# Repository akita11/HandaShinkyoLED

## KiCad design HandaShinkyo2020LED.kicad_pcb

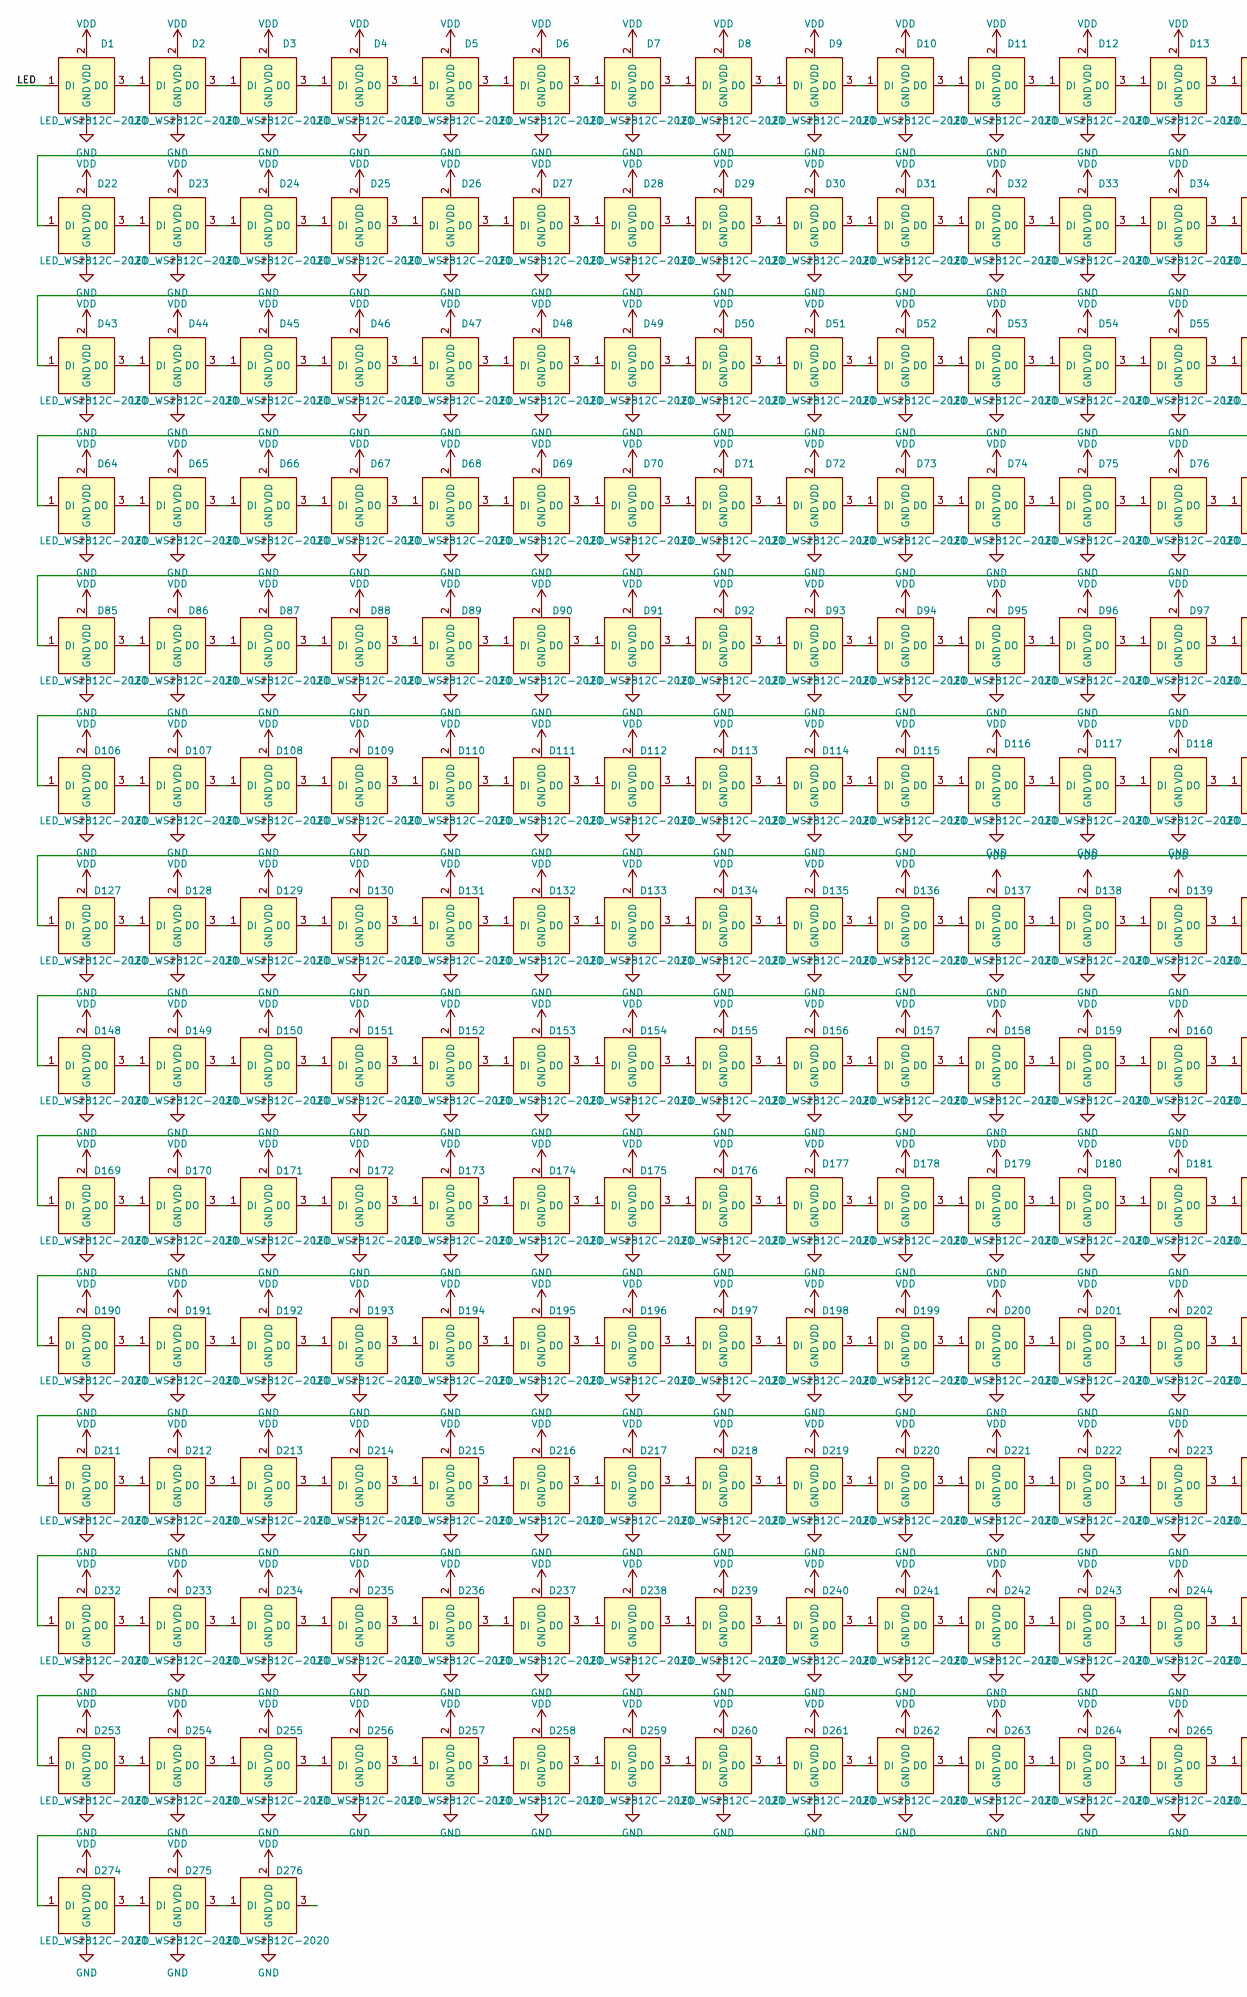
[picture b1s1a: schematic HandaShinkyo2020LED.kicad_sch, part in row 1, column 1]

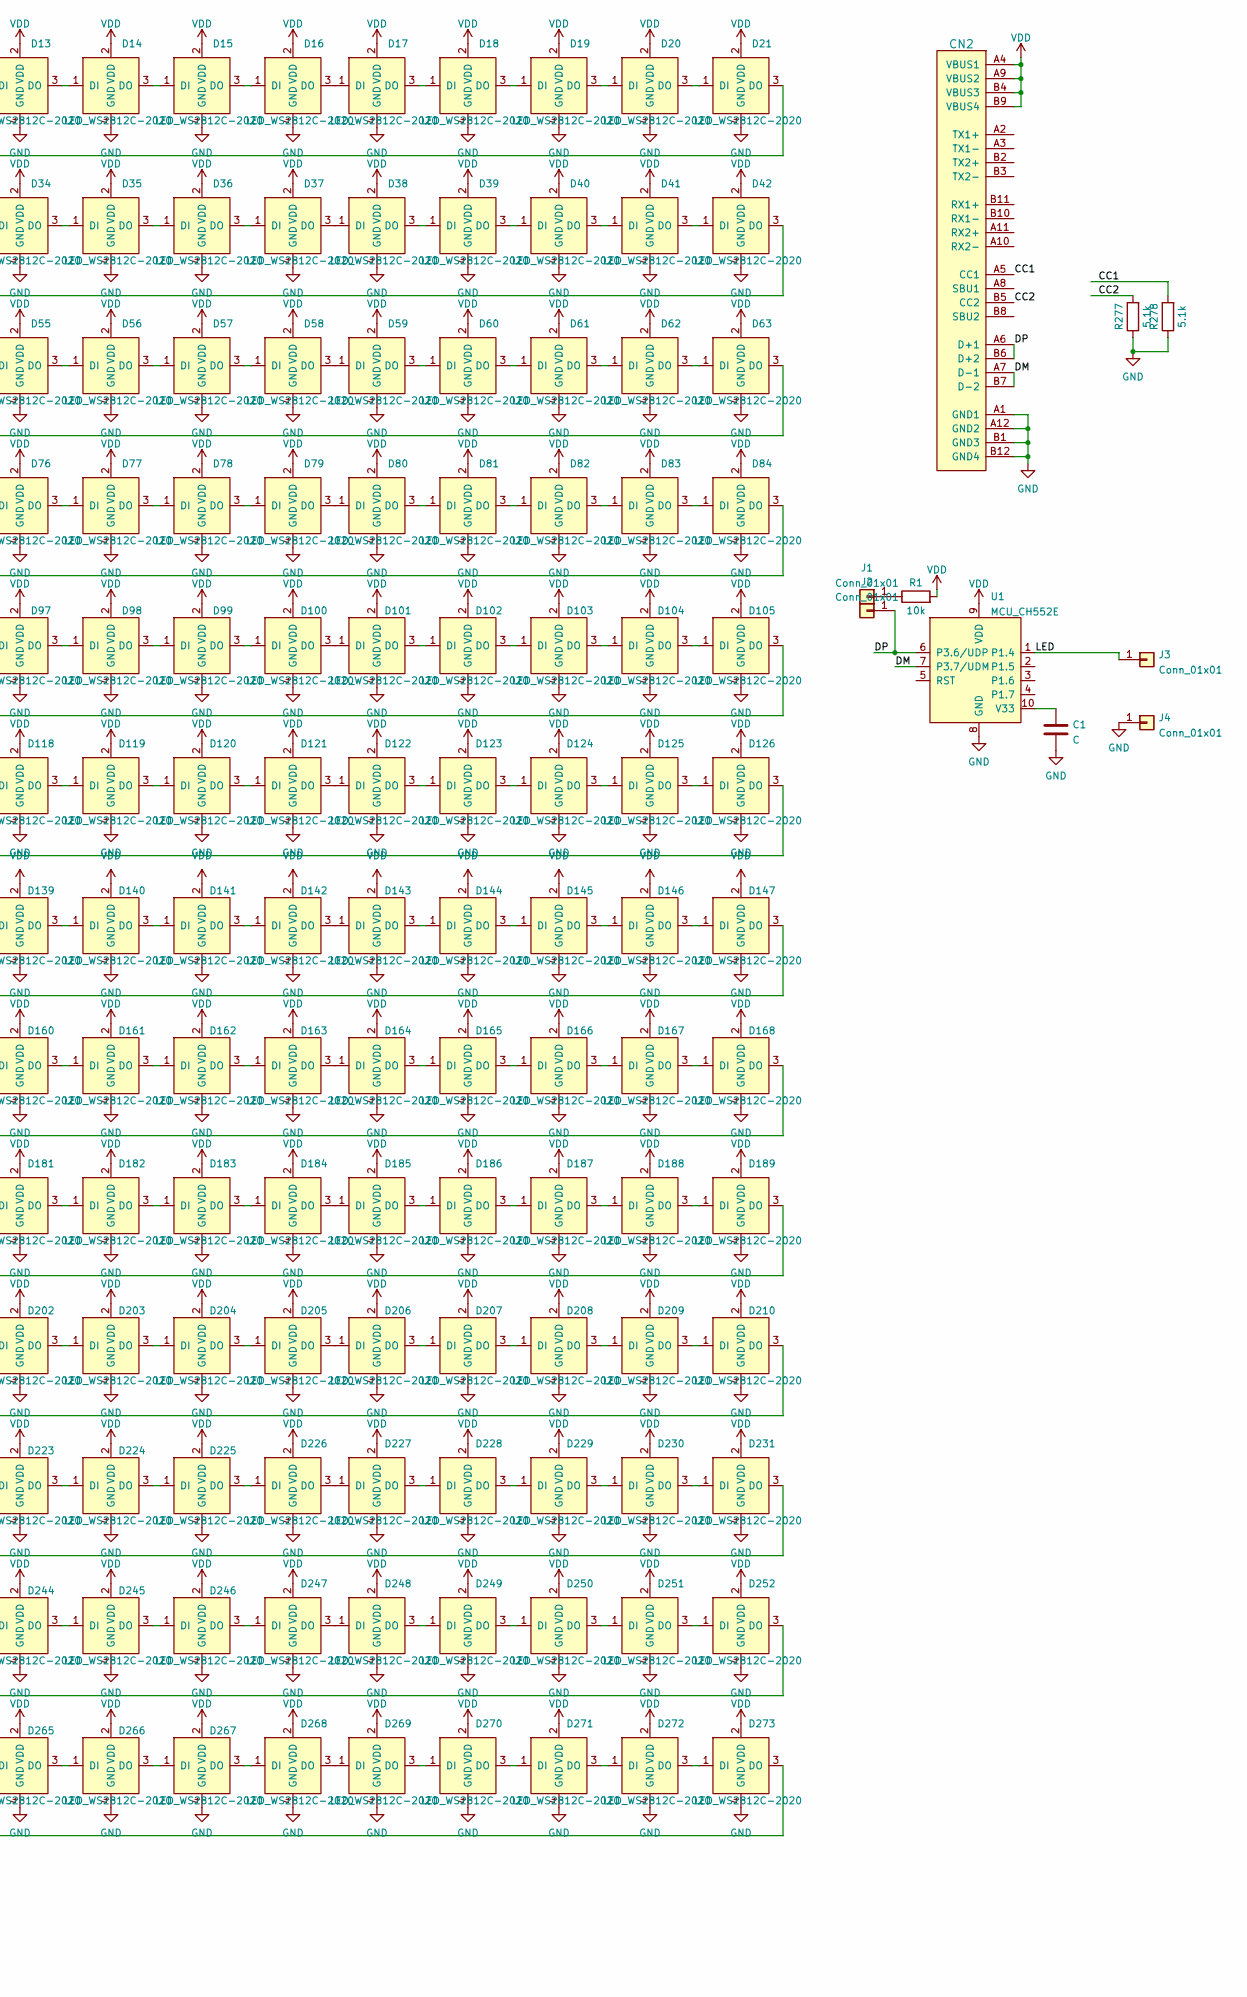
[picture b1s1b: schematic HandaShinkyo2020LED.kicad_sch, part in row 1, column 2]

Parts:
C1: C; C_0603_1608Metric
CN2: CON_USB-CPCBPLUG; USB-C_PCBPLUG
D1, D2, D3, D4, D5, D6, D7, D8, D9, D10, D11, D12, D13, D14, D15, D16, D17, D18, D19, D20, D21, D22, D23, D24, D25, D26, D27, D28, D29, D30, D31, D32, D33, D34, D35, D36, D37, D38, D39, D40, D41, D42, D43, D44, D45, D46, D47, D48, D49, D50, D51, D52, D53, D54, D55, D56, D57, D58, D59, D60, D61, D62, D63, D64, D65, D66, D67, D68, D69, D70, D71, D72, D73, D74, D75, D76, D77, D78, D79, D80, D81, D82, D83, D84, D85, D86, D87, D88, D89, D90, D91, D92, D93, D94, D95, D96, D97, D98, D99, D100, D101, D102, D103, D104, D105, D106, D107, D108, D109, D110, D111, D112, D113, D114, D115, D116, D117, D118, D119, D120, D121, D122, D123, D124, D125, D126, D127, D128, D129, D130, D131, D132, D133, D134, D135, D136, D137, D138, D139, D140, D141, D142, D143, D144, D145, D146, D147, D148, D149, D150, D151, D152, D153, D154, D155, D156, D157, D158, D159, D160, D161, D162, D163, D164, D165, D166, D167, D168, D169, D170, D171, D172, D173, D174, D175, D176, D177, D178, D179, D180, D181, D182, D183, D184, D185, D186, D187, D188, D189, D190, D191, D192, D193, D194, D195, D196, D197, D198, D199, D200, D201, D202, D203, D204, D205, D206, D207, D208, D209, D210, D211, D212, D213, D214, D215, D216, D217, D218, D219, D220, D221, D222, D223, D224, D225, D226, D227, D228, D229, D230, D231, D232, D233, D234, D235, D236, D237, D238, D239, D240, D241, D242, D243, D244, D245, D246, D247, D248, D249, D250, D251, D252, D253, D254, D255, D256, D257, D258, D259, D260, D261, D262, D263, D264, D265, D266, D267, D268, D269, D270, D271, D272, D273, D274, D275, D276: LED_WS2812C-2020; LED_2020_4p
J1, J2, J3, J4: Conn_01x01; Pad_SMD1.6mm
R1: 10k; R_0603_1608Metric
R277, R278: 5.1k; R_0603_1608Metric
U1: MCU_CH552E; TSSOP-10_3x3mm_P0.5mm

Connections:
/CC1: CN2.A5 (CC1), R278.2
/CC2: CN2.B5 (CC2), R277.2
/DM: CN2.A7 (D-1), CN2.B7 (D-2), U1.7 (P3.7/UDM)
/DP: CN2.A6 (D+1), CN2.B6 (D+2), J2.1, U1.6 (P3.6/UDP)
/LED: D1.1 (DI), J3.1, U1.1 (P1.4)
GND: C1.2, CN2.A1 (GND1), CN2.A12 (GND2), CN2.B1 (GND3), CN2.B12 (GND4), D1.4 (GND), D2.4 (GND), D3.4 (GND), D4.4 (GND), D5.4 (GND), D6.4 (GND), D7.4 (GND), D8.4 (GND), D9.4 (GND), D10.4 (GND), D11.4 (GND), D12.4 (GND), D13.4 (GND), D14.4 (GND), D15.4 (GND), D16.4 (GND), D17.4 (GND), D18.4 (GND), D19.4 (GND), D20.4 (GND), D21.4 (GND), D22.4 (GND), D23.4 (GND), D24.4 (GND), D25.4 (GND), D26.4 (GND), D27.4 (GND), D28.4 (GND), D29.4 (GND), D30.4 (GND), D31.4 (GND), D32.4 (GND), D33.4 (GND), D34.4 (GND), D35.4 (GND), D36.4 (GND), D37.4 (GND), D38.4 (GND), D39.4 (GND), D40.4 (GND), D41.4 (GND), D42.4 (GND), D43.4 (GND), D44.4 (GND), D45.4 (GND), D46.4 (GND), D47.4 (GND), D48.4 (GND), D49.4 (GND), D50.4 (GND), D51.4 (GND), D52.4 (GND), D53.4 (GND), D54.4 (GND), D55.4 (GND), D56.4 (GND), D57.4 (GND), D58.4 (GND), D59.4 (GND), D60.4 (GND), D61.4 (GND), D62.4 (GND), D63.4 (GND), D64.4 (GND), D65.4 (GND), D66.4 (GND), D67.4 (GND), D68.4 (GND), D69.4 (GND), D70.4 (GND), D71.4 (GND), D72.4 (GND), D73.4 (GND), D74.4 (GND), D75.4 (GND), D76.4 (GND), D77.4 (GND), D78.4 (GND), D79.4 (GND), D80.4 (GND), D81.4 (GND), D82.4 (GND), D83.4 (GND), D84.4 (GND), D85.4 (GND), D86.4 (GND), D87.4 (GND), D88.4 (GND), D89.4 (GND), D90.4 (GND), D91.4 (GND), D92.4 (GND), D93.4 (GND), D94.4 (GND), D95.4 (GND), D96.4 (GND), D97.4 (GND), D98.4 (GND), D99.4 (GND), D100.4 (GND), D101.4 (GND), D102.4 (GND), D103.4 (GND), D104.4 (GND), D105.4 (GND), D106.4 (GND), D107.4 (GND), D108.4 (GND), D109.4 (GND), D110.4 (GND), D111.4 (GND), D112.4 (GND), D113.4 (GND), D114.4 (GND), D115.4 (GND), D116.4 (GND), D117.4 (GND), D118.4 (GND), D119.4 (GND), D120.4 (GND), D121.4 (GND), D122.4 (GND), D123.4 (GND), D124.4 (GND), D125.4 (GND), D126.4 (GND), D127.4 (GND), D128.4 (GND), D129.4 (GND), D130.4 (GND), D131.4 (GND), D132.4 (GND), D133.4 (GND), D134.4 (GND), D135.4 (GND), D136.4 (GND), D137.4 (GND), D138.4 (GND), D139.4 (GND), D140.4 (GND), D141.4 (GND), D142.4 (GND), D143.4 (GND), D144.4 (GND), D145.4 (GND), D146.4 (GND), D147.4 (GND), D148.4 (GND), D149.4 (GND), D150.4 (GND), D151.4 (GND), D152.4 (GND), D153.4 (GND), D154.4 (GND), D155.4 (GND), D156.4 (GND), D157.4 (GND), D158.4 (GND), D159.4 (GND), D160.4 (GND), D161.4 (GND), D162.4 (GND), D163.4 (GND), D164.4 (GND), D165.4 (GND), D166.4 (GND), D167.4 (GND), D168.4 (GND), D169.4 (GND), D170.4 (GND), D171.4 (GND), D172.4 (GND), D173.4 (GND), D174.4 (GND), D175.4 (GND), D176.4 (GND), D177.4 (GND), D178.4 (GND), D179.4 (GND), D180.4 (GND), D181.4 (GND), D182.4 (GND), D183.4 (GND), D184.4 (GND), D185.4 (GND), D186.4 (GND), D187.4 (GND), D188.4 (GND), D189.4 (GND), D190.4 (GND), D191.4 (GND), D192.4 (GND), D193.4 (GND), D194.4 (GND), D195.4 (GND), D196.4 (GND), D197.4 (GND), D198.4 (GND), D199.4 (GND), D200.4 (GND), D201.4 (GND), D202.4 (GND), D203.4 (GND), D204.4 (GND), D205.4 (GND), D206.4 (GND), D207.4 (GND), D208.4 (GND), D209.4 (GND), D210.4 (GND), D211.4 (GND), D212.4 (GND), D213.4 (GND), D214.4 (GND), D215.4 (GND), D216.4 (GND), D217.4 (GND), D218.4 (GND), D219.4 (GND), D220.4 (GND), D221.4 (GND), D222.4 (GND), D223.4 (GND), D224.4 (GND), D225.4 (GND), D226.4 (GND), D227.4 (GND), D228.4 (GND), D229.4 (GND), D230.4 (GND), D231.4 (GND), D232.4 (GND), D233.4 (GND), D234.4 (GND), D235.4 (GND), D236.4 (GND), D237.4 (GND), D238.4 (GND), D239.4 (GND), D240.4 (GND), D241.4 (GND), D242.4 (GND), D243.4 (GND), D244.4 (GND), D245.4 (GND), D246.4 (GND), D247.4 (GND), D248.4 (GND), D249.4 (GND), D250.4 (GND), D251.4 (GND), D252.4 (GND), D253.4 (GND), D254.4 (GND), D255.4 (GND), D256.4 (GND), D257.4 (GND), D258.4 (GND), D259.4 (GND), D260.4 (GND), D261.4 (GND), D262.4 (GND), D263.4 (GND), D264.4 (GND), D265.4 (GND), D266.4 (GND), D267.4 (GND), D268.4 (GND), D269.4 (GND), D270.4 (GND), D271.4 (GND), D272.4 (GND), D273.4 (GND), D274.4 (GND), D275.4 (GND), D276.4 (GND), J4.1, R277.1, R278.1, U1.8 (GND)
unnamed: C1.1, U1.10 (V33)
unnamed: D1.3 (DO), D2.1 (DI)
unnamed: D2.3 (DO), D3.1 (DI)
unnamed: D3.3 (DO), D4.1 (DI)
unnamed: D4.3 (DO), D5.1 (DI)
unnamed: D5.3 (DO), D6.1 (DI)
unnamed: D6.3 (DO), D7.1 (DI)
unnamed: D7.3 (DO), D8.1 (DI)
unnamed: D8.3 (DO), D9.1 (DI)
unnamed: D9.3 (DO), D10.1 (DI)
unnamed: D10.3 (DO), D11.1 (DI)
unnamed: D11.3 (DO), D12.1 (DI)
unnamed: D12.3 (DO), D13.1 (DI)
unnamed: D13.3 (DO), D14.1 (DI)
unnamed: D14.3 (DO), D15.1 (DI)
unnamed: D15.3 (DO), D16.1 (DI)
unnamed: D16.3 (DO), D17.1 (DI)
unnamed: D17.3 (DO), D18.1 (DI)
unnamed: D18.3 (DO), D19.1 (DI)
unnamed: D19.3 (DO), D20.1 (DI)
unnamed: D20.3 (DO), D21.1 (DI)
unnamed: D21.3 (DO), D22.1 (DI)
unnamed: D22.3 (DO), D23.1 (DI)
unnamed: D23.3 (DO), D24.1 (DI)
unnamed: D24.3 (DO), D25.1 (DI)
unnamed: D25.3 (DO), D26.1 (DI)
unnamed: D26.3 (DO), D27.1 (DI)
unnamed: D27.3 (DO), D28.1 (DI)
unnamed: D28.3 (DO), D29.1 (DI)
unnamed: D29.3 (DO), D30.1 (DI)
unnamed: D30.3 (DO), D31.1 (DI)
unnamed: D31.3 (DO), D32.1 (DI)
unnamed: D32.3 (DO), D33.1 (DI)
unnamed: D33.3 (DO), D34.1 (DI)
unnamed: D34.3 (DO), D35.1 (DI)
unnamed: D35.3 (DO), D36.1 (DI)
unnamed: D36.3 (DO), D37.1 (DI)
unnamed: D37.3 (DO), D38.1 (DI)
unnamed: D38.3 (DO), D39.1 (DI)
unnamed: D39.3 (DO), D40.1 (DI)
unnamed: D40.3 (DO), D41.1 (DI)
unnamed: D41.3 (DO), D42.1 (DI)
unnamed: D42.3 (DO), D43.1 (DI)
unnamed: D43.3 (DO), D44.1 (DI)
unnamed: D44.3 (DO), D45.1 (DI)
unnamed: D45.3 (DO), D46.1 (DI)
unnamed: D46.3 (DO), D47.1 (DI)
unnamed: D47.3 (DO), D48.1 (DI)
unnamed: D48.3 (DO), D49.1 (DI)
unnamed: D49.3 (DO), D50.1 (DI)
unnamed: D50.3 (DO), D51.1 (DI)
unnamed: D51.3 (DO), D52.1 (DI)
unnamed: D52.3 (DO), D53.1 (DI)
unnamed: D53.3 (DO), D54.1 (DI)
unnamed: D54.3 (DO), D55.1 (DI)
unnamed: D55.3 (DO), D56.1 (DI)
unnamed: D56.3 (DO), D57.1 (DI)
unnamed: D57.3 (DO), D58.1 (DI)
unnamed: D58.3 (DO), D59.1 (DI)
unnamed: D59.3 (DO), D60.1 (DI)
unnamed: D60.3 (DO), D61.1 (DI)
unnamed: D61.3 (DO), D62.1 (DI)
unnamed: D62.3 (DO), D63.1 (DI)
unnamed: D63.3 (DO), D64.1 (DI)
unnamed: D64.3 (DO), D65.1 (DI)
unnamed: D65.3 (DO), D66.1 (DI)
unnamed: D66.3 (DO), D67.1 (DI)
unnamed: D67.3 (DO), D68.1 (DI)
unnamed: D68.3 (DO), D69.1 (DI)
unnamed: D69.3 (DO), D70.1 (DI)
unnamed: D70.3 (DO), D71.1 (DI)
unnamed: D71.3 (DO), D72.1 (DI)
unnamed: D72.3 (DO), D73.1 (DI)
unnamed: D73.3 (DO), D74.1 (DI)
unnamed: D74.3 (DO), D75.1 (DI)
unnamed: D75.3 (DO), D76.1 (DI)
unnamed: D76.3 (DO), D77.1 (DI)
unnamed: D77.3 (DO), D78.1 (DI)
unnamed: D78.3 (DO), D79.1 (DI)
unnamed: D79.3 (DO), D80.1 (DI)
unnamed: D80.3 (DO), D81.1 (DI)
unnamed: D81.3 (DO), D82.1 (DI)
unnamed: D82.3 (DO), D83.1 (DI)
unnamed: D83.3 (DO), D84.1 (DI)
unnamed: D84.3 (DO), D85.1 (DI)
unnamed: D85.3 (DO), D86.1 (DI)
unnamed: D86.3 (DO), D87.1 (DI)
unnamed: D87.3 (DO), D88.1 (DI)
unnamed: D88.3 (DO), D89.1 (DI)
unnamed: D89.3 (DO), D90.1 (DI)
unnamed: D90.3 (DO), D91.1 (DI)
unnamed: D91.3 (DO), D92.1 (DI)
unnamed: D92.3 (DO), D93.1 (DI)
unnamed: D93.3 (DO), D94.1 (DI)
unnamed: D94.3 (DO), D95.1 (DI)
unnamed: D95.3 (DO), D96.1 (DI)
unnamed: D96.3 (DO), D97.1 (DI)
unnamed: D97.3 (DO), D98.1 (DI)
unnamed: D98.3 (DO), D99.1 (DI)
unnamed: D99.3 (DO), D100.1 (DI)
unnamed: D100.3 (DO), D101.1 (DI)
unnamed: D101.3 (DO), D102.1 (DI)
unnamed: D102.3 (DO), D103.1 (DI)
unnamed: D103.3 (DO), D104.1 (DI)
unnamed: D104.3 (DO), D105.1 (DI)
unnamed: D105.3 (DO), D106.1 (DI)
unnamed: D106.3 (DO), D107.1 (DI)
unnamed: D107.3 (DO), D108.1 (DI)
unnamed: D108.3 (DO), D109.1 (DI)
unnamed: D109.3 (DO), D110.1 (DI)
unnamed: D110.3 (DO), D111.1 (DI)
unnamed: D111.3 (DO), D112.1 (DI)
unnamed: D112.3 (DO), D113.1 (DI)
unnamed: D113.3 (DO), D114.1 (DI)
unnamed: D114.3 (DO), D115.1 (DI)
unnamed: D115.3 (DO), D116.1 (DI)
unnamed: D116.3 (DO), D117.1 (DI)
unnamed: D117.3 (DO), D118.1 (DI)
unnamed: D118.3 (DO), D119.1 (DI)
unnamed: D119.3 (DO), D120.1 (DI)
unnamed: D120.3 (DO), D121.1 (DI)
unnamed: D121.3 (DO), D122.1 (DI)
unnamed: D122.3 (DO), D123.1 (DI)
unnamed: D123.3 (DO), D124.1 (DI)
unnamed: D124.3 (DO), D125.1 (DI)
unnamed: D125.3 (DO), D126.1 (DI)
unnamed: D126.3 (DO), D127.1 (DI)
unnamed: D127.3 (DO), D128.1 (DI)
unnamed: D128.3 (DO), D129.1 (DI)
unnamed: D129.3 (DO), D130.1 (DI)
unnamed: D130.3 (DO), D131.1 (DI)
unnamed: D131.3 (DO), D132.1 (DI)
unnamed: D132.3 (DO), D133.1 (DI)
unnamed: D133.3 (DO), D134.1 (DI)
unnamed: D134.3 (DO), D135.1 (DI)
unnamed: D135.3 (DO), D136.1 (DI)
unnamed: D136.3 (DO), D137.1 (DI)
unnamed: D137.3 (DO), D138.1 (DI)
unnamed: D138.3 (DO), D139.1 (DI)
unnamed: D139.3 (DO), D140.1 (DI)
unnamed: D140.3 (DO), D141.1 (DI)
unnamed: D141.3 (DO), D142.1 (DI)
unnamed: D142.3 (DO), D143.1 (DI)
unnamed: D143.3 (DO), D144.1 (DI)
unnamed: D144.3 (DO), D145.1 (DI)
unnamed: D145.3 (DO), D146.1 (DI)
unnamed: D146.3 (DO), D147.1 (DI)
unnamed: D147.3 (DO), D148.1 (DI)
unnamed: D148.3 (DO), D149.1 (DI)
unnamed: D149.3 (DO), D150.1 (DI)
unnamed: D150.3 (DO), D151.1 (DI)
unnamed: D151.3 (DO), D152.1 (DI)
unnamed: D152.3 (DO), D153.1 (DI)
unnamed: D153.3 (DO), D154.1 (DI)
unnamed: D154.3 (DO), D155.1 (DI)
unnamed: D155.3 (DO), D156.1 (DI)
unnamed: D156.3 (DO), D157.1 (DI)
unnamed: D157.3 (DO), D158.1 (DI)
unnamed: D158.3 (DO), D159.1 (DI)
unnamed: D159.3 (DO), D160.1 (DI)
unnamed: D160.3 (DO), D161.1 (DI)
unnamed: D161.3 (DO), D162.1 (DI)
unnamed: D162.3 (DO), D163.1 (DI)
unnamed: D163.3 (DO), D164.1 (DI)
unnamed: D164.3 (DO), D165.1 (DI)
unnamed: D165.3 (DO), D166.1 (DI)
unnamed: D166.3 (DO), D167.1 (DI)
unnamed: D167.3 (DO), D168.1 (DI)
unnamed: D168.3 (DO), D169.1 (DI)
unnamed: D169.3 (DO), D170.1 (DI)
unnamed: D170.3 (DO), D171.1 (DI)
unnamed: D171.3 (DO), D172.1 (DI)
unnamed: D172.3 (DO), D173.1 (DI)
unnamed: D173.3 (DO), D174.1 (DI)
unnamed: D174.3 (DO), D175.1 (DI)
unnamed: D175.3 (DO), D176.1 (DI)
unnamed: D176.3 (DO), D177.1 (DI)
unnamed: D177.3 (DO), D178.1 (DI)
unnamed: D178.3 (DO), D179.1 (DI)
unnamed: D179.3 (DO), D180.1 (DI)
unnamed: D180.3 (DO), D181.1 (DI)
unnamed: D181.3 (DO), D182.1 (DI)
unnamed: D182.3 (DO), D183.1 (DI)
unnamed: D183.3 (DO), D184.1 (DI)
unnamed: D184.3 (DO), D185.1 (DI)
unnamed: D185.3 (DO), D186.1 (DI)
unnamed: D186.3 (DO), D187.1 (DI)
unnamed: D187.3 (DO), D188.1 (DI)
unnamed: D188.3 (DO), D189.1 (DI)
unnamed: D189.3 (DO), D190.1 (DI)
unnamed: D190.3 (DO), D191.1 (DI)
unnamed: D191.3 (DO), D192.1 (DI)
unnamed: D192.3 (DO), D193.1 (DI)
unnamed: D193.3 (DO), D194.1 (DI)
unnamed: D194.3 (DO), D195.1 (DI)
unnamed: D195.3 (DO), D196.1 (DI)
unnamed: D196.3 (DO), D197.1 (DI)
unnamed: D197.3 (DO), D198.1 (DI)
unnamed: D198.3 (DO), D199.1 (DI)
unnamed: D199.3 (DO), D200.1 (DI)
unnamed: D200.3 (DO), D201.1 (DI)
unnamed: D201.3 (DO), D202.1 (DI)
unnamed: D202.3 (DO), D203.1 (DI)
unnamed: D203.3 (DO), D204.1 (DI)
unnamed: D204.3 (DO), D205.1 (DI)
unnamed: D205.3 (DO), D206.1 (DI)
unnamed: D206.3 (DO), D207.1 (DI)
unnamed: D207.3 (DO), D208.1 (DI)
unnamed: D208.3 (DO), D209.1 (DI)
unnamed: D209.3 (DO), D210.1 (DI)
unnamed: D210.3 (DO), D211.1 (DI)
unnamed: D211.3 (DO), D212.1 (DI)
unnamed: D212.3 (DO), D213.1 (DI)
unnamed: D213.3 (DO), D214.1 (DI)
unnamed: D214.3 (DO), D215.1 (DI)
unnamed: D215.3 (DO), D216.1 (DI)
unnamed: D216.3 (DO), D217.1 (DI)
unnamed: D217.3 (DO), D218.1 (DI)
unnamed: D218.3 (DO), D219.1 (DI)
unnamed: D219.3 (DO), D220.1 (DI)
unnamed: D220.3 (DO), D221.1 (DI)
unnamed: D221.3 (DO), D222.1 (DI)
unnamed: D222.3 (DO), D223.1 (DI)
unnamed: D223.3 (DO), D224.1 (DI)
unnamed: D224.3 (DO), D225.1 (DI)
unnamed: D225.3 (DO), D226.1 (DI)
unnamed: D226.3 (DO), D227.1 (DI)
unnamed: D227.3 (DO), D228.1 (DI)
unnamed: D228.3 (DO), D229.1 (DI)
unnamed: D229.3 (DO), D230.1 (DI)
unnamed: D230.3 (DO), D231.1 (DI)
unnamed: D231.3 (DO), D232.1 (DI)
unnamed: D232.3 (DO), D233.1 (DI)
unnamed: D233.3 (DO), D234.1 (DI)
unnamed: D234.3 (DO), D235.1 (DI)
unnamed: D235.3 (DO), D236.1 (DI)
unnamed: D236.3 (DO), D237.1 (DI)
unnamed: D237.3 (DO), D238.1 (DI)
unnamed: D238.3 (DO), D239.1 (DI)
unnamed: D239.3 (DO), D240.1 (DI)
unnamed: D240.3 (DO), D241.1 (DI)
unnamed: D241.3 (DO), D242.1 (DI)
unnamed: D242.3 (DO), D243.1 (DI)
unnamed: D243.3 (DO), D244.1 (DI)
unnamed: D244.3 (DO), D245.1 (DI)
unnamed: D245.3 (DO), D246.1 (DI)
unnamed: D246.3 (DO), D247.1 (DI)
unnamed: D247.3 (DO), D248.1 (DI)
unnamed: D248.3 (DO), D249.1 (DI)
unnamed: D249.3 (DO), D250.1 (DI)
unnamed: D250.3 (DO), D251.1 (DI)
unnamed: D251.3 (DO), D252.1 (DI)
unnamed: D252.3 (DO), D253.1 (DI)
unnamed: D253.3 (DO), D254.1 (DI)
unnamed: D254.3 (DO), D255.1 (DI)
unnamed: D255.3 (DO), D256.1 (DI)
unnamed: D256.3 (DO), D257.1 (DI)
unnamed: D257.3 (DO), D258.1 (DI)
unnamed: D258.3 (DO), D259.1 (DI)
unnamed: D259.3 (DO), D260.1 (DI)
unnamed: D260.3 (DO), D261.1 (DI)
unnamed: D261.3 (DO), D262.1 (DI)
unnamed: D262.3 (DO), D263.1 (DI)
unnamed: D263.3 (DO), D264.1 (DI)
unnamed: D264.3 (DO), D265.1 (DI)
unnamed: D265.3 (DO), D266.1 (DI)
unnamed: D266.3 (DO), D267.1 (DI)
unnamed: D267.3 (DO), D268.1 (DI)
unnamed: D268.3 (DO), D269.1 (DI)
unnamed: D269.3 (DO), D270.1 (DI)
unnamed: D270.3 (DO), D271.1 (DI)
unnamed: D271.3 (DO), D272.1 (DI)
unnamed: D272.3 (DO), D273.1 (DI)
unnamed: D273.3 (DO), D274.1 (DI)
unnamed: D274.3 (DO), D275.1 (DI)
unnamed: D275.3 (DO), D276.1 (DI)
unnamed: J1.1, R1.1
VDD: CN2.A4 (VBUS1), CN2.A9 (VBUS2), CN2.B4 (VBUS3), CN2.B9 (VBUS4), D1.2 (VDD), D2.2 (VDD), D3.2 (VDD), D4.2 (VDD), D5.2 (VDD), D6.2 (VDD), D7.2 (VDD), D8.2 (VDD), D9.2 (VDD), D10.2 (VDD), D11.2 (VDD), D12.2 (VDD), D13.2 (VDD), D14.2 (VDD), D15.2 (VDD), D16.2 (VDD), D17.2 (VDD), D18.2 (VDD), D19.2 (VDD), D20.2 (VDD), D21.2 (VDD), D22.2 (VDD), D23.2 (VDD), D24.2 (VDD), D25.2 (VDD), D26.2 (VDD), D27.2 (VDD), D28.2 (VDD), D29.2 (VDD), D30.2 (VDD), D31.2 (VDD), D32.2 (VDD), D33.2 (VDD), D34.2 (VDD), D35.2 (VDD), D36.2 (VDD), D37.2 (VDD), D38.2 (VDD), D39.2 (VDD), D40.2 (VDD), D41.2 (VDD), D42.2 (VDD), D43.2 (VDD), D44.2 (VDD), D45.2 (VDD), D46.2 (VDD), D47.2 (VDD), D48.2 (VDD), D49.2 (VDD), D50.2 (VDD), D51.2 (VDD), D52.2 (VDD), D53.2 (VDD), D54.2 (VDD), D55.2 (VDD), D56.2 (VDD), D57.2 (VDD), D58.2 (VDD), D59.2 (VDD), D60.2 (VDD), D61.2 (VDD), D62.2 (VDD), D63.2 (VDD), D64.2 (VDD), D65.2 (VDD), D66.2 (VDD), D67.2 (VDD), D68.2 (VDD), D69.2 (VDD), D70.2 (VDD), D71.2 (VDD), D72.2 (VDD), D73.2 (VDD), D74.2 (VDD), D75.2 (VDD), D76.2 (VDD), D77.2 (VDD), D78.2 (VDD), D79.2 (VDD), D80.2 (VDD), D81.2 (VDD), D82.2 (VDD), D83.2 (VDD), D84.2 (VDD), D85.2 (VDD), D86.2 (VDD), D87.2 (VDD), D88.2 (VDD), D89.2 (VDD), D90.2 (VDD), D91.2 (VDD), D92.2 (VDD), D93.2 (VDD), D94.2 (VDD), D95.2 (VDD), D96.2 (VDD), D97.2 (VDD), D98.2 (VDD), D99.2 (VDD), D100.2 (VDD), D101.2 (VDD), D102.2 (VDD), D103.2 (VDD), D104.2 (VDD), D105.2 (VDD), D106.2 (VDD), D107.2 (VDD), D108.2 (VDD), D109.2 (VDD), D110.2 (VDD), D111.2 (VDD), D112.2 (VDD), D113.2 (VDD), D114.2 (VDD), D115.2 (VDD), D116.2 (VDD), D117.2 (VDD), D118.2 (VDD), D119.2 (VDD), D120.2 (VDD), D121.2 (VDD), D122.2 (VDD), D123.2 (VDD), D124.2 (VDD), D125.2 (VDD), D126.2 (VDD), D127.2 (VDD), D128.2 (VDD), D129.2 (VDD), D130.2 (VDD), D131.2 (VDD), D132.2 (VDD), D133.2 (VDD), D134.2 (VDD), D135.2 (VDD), D136.2 (VDD), D137.2 (VDD), D138.2 (VDD), D139.2 (VDD), D140.2 (VDD), D141.2 (VDD), D142.2 (VDD), D143.2 (VDD), D144.2 (VDD), D145.2 (VDD), D146.2 (VDD), D147.2 (VDD), D148.2 (VDD), D149.2 (VDD), D150.2 (VDD), D151.2 (VDD), D152.2 (VDD), D153.2 (VDD), D154.2 (VDD), D155.2 (VDD), D156.2 (VDD), D157.2 (VDD), D158.2 (VDD), D159.2 (VDD), D160.2 (VDD), D161.2 (VDD), D162.2 (VDD), D163.2 (VDD), D164.2 (VDD), D165.2 (VDD), D166.2 (VDD), D167.2 (VDD), D168.2 (VDD), D169.2 (VDD), D170.2 (VDD), D171.2 (VDD), D172.2 (VDD), D173.2 (VDD), D174.2 (VDD), D175.2 (VDD), D176.2 (VDD), D177.2 (VDD), D178.2 (VDD), D179.2 (VDD), D180.2 (VDD), D181.2 (VDD), D182.2 (VDD), D183.2 (VDD), D184.2 (VDD), D185.2 (VDD), D186.2 (VDD), D187.2 (VDD), D188.2 (VDD), D189.2 (VDD), D190.2 (VDD), D191.2 (VDD), D192.2 (VDD), D193.2 (VDD), D194.2 (VDD), D195.2 (VDD), D196.2 (VDD), D197.2 (VDD), D198.2 (VDD), D199.2 (VDD), D200.2 (VDD), D201.2 (VDD), D202.2 (VDD), D203.2 (VDD), D204.2 (VDD), D205.2 (VDD), D206.2 (VDD), D207.2 (VDD), D208.2 (VDD), D209.2 (VDD), D210.2 (VDD), D211.2 (VDD), D212.2 (VDD), D213.2 (VDD), D214.2 (VDD), D215.2 (VDD), D216.2 (VDD), D217.2 (VDD), D218.2 (VDD), D219.2 (VDD), D220.2 (VDD), D221.2 (VDD), D222.2 (VDD), D223.2 (VDD), D224.2 (VDD), D225.2 (VDD), D226.2 (VDD), D227.2 (VDD), D228.2 (VDD), D229.2 (VDD), D230.2 (VDD), D231.2 (VDD), D232.2 (VDD), D233.2 (VDD), D234.2 (VDD), D235.2 (VDD), D236.2 (VDD), D237.2 (VDD), D238.2 (VDD), D239.2 (VDD), D240.2 (VDD), D241.2 (VDD), D242.2 (VDD), D243.2 (VDD), D244.2 (VDD), D245.2 (VDD), D246.2 (VDD), D247.2 (VDD), D248.2 (VDD), D249.2 (VDD), D250.2 (VDD), D251.2 (VDD), D252.2 (VDD), D253.2 (VDD), D254.2 (VDD), D255.2 (VDD), D256.2 (VDD), D257.2 (VDD), D258.2 (VDD), D259.2 (VDD), D260.2 (VDD), D261.2 (VDD), D262.2 (VDD), D263.2 (VDD), D264.2 (VDD), D265.2 (VDD), D266.2 (VDD), D267.2 (VDD), D268.2 (VDD), D269.2 (VDD), D270.2 (VDD), D271.2 (VDD), D272.2 (VDD), D273.2 (VDD), D274.2 (VDD), D275.2 (VDD), D276.2 (VDD), R1.2, U1.9 (VDD)

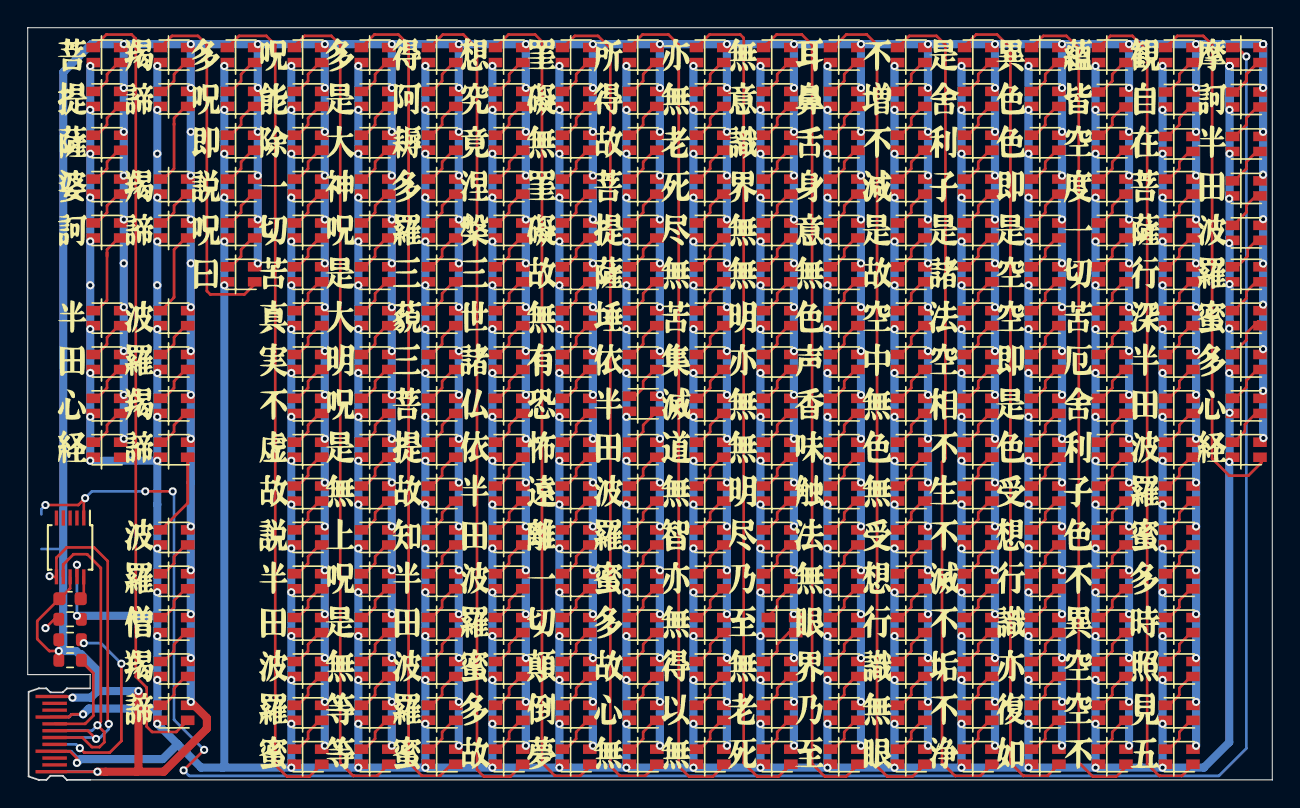
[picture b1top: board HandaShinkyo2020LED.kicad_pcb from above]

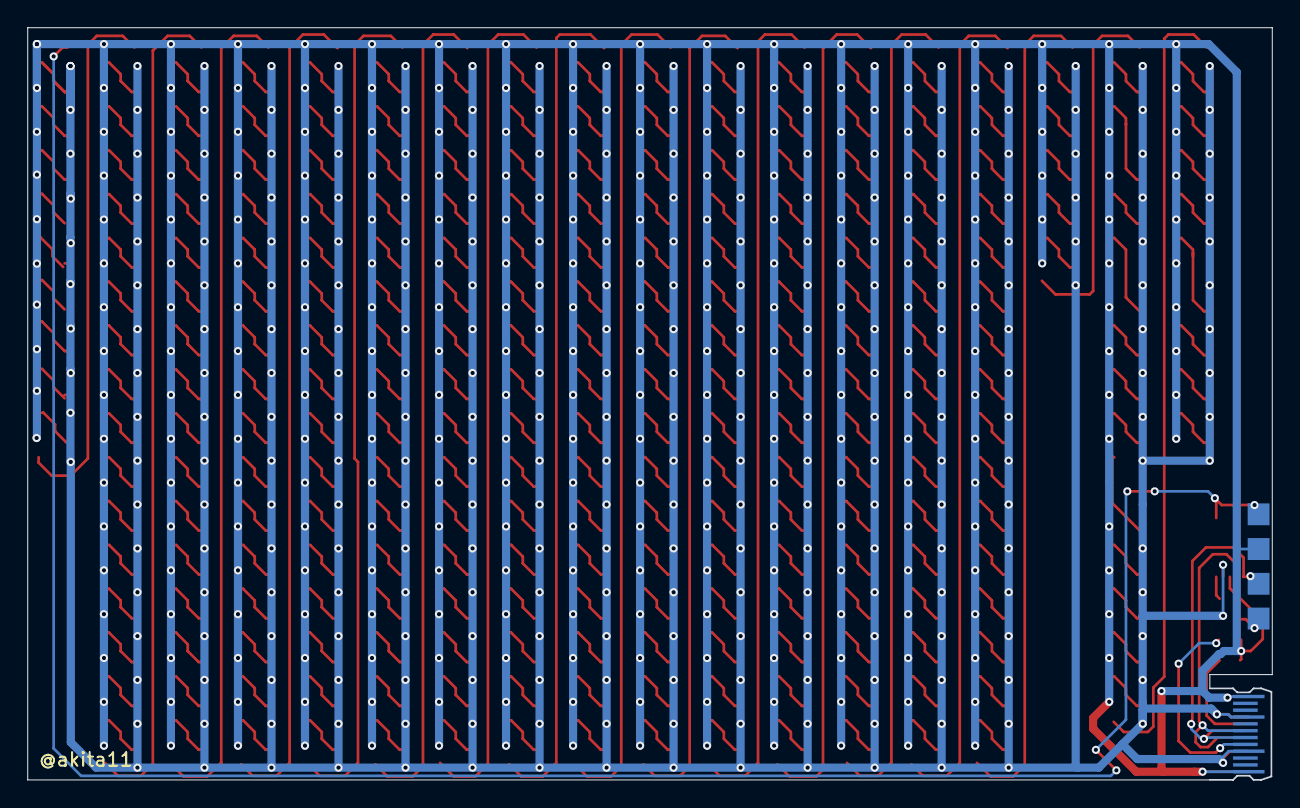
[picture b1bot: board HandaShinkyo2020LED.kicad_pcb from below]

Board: 2 copper layers, 91.0 x 55.0 mm, 286 parts (4 on the bottom side), 284 nets.
